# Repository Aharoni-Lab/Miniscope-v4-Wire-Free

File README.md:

# Miniscope-v4-Wire-Free

The Miniscope v4 Wire-Free is an open-source one photon miniatirized microscope for neural recordings in freely behaving animals.  

This microscope is based on the Miniscope v4, sharing the same optical properties with redesigned electronics. For more information check our wiki page: https://wiki.aharoni-lab.com/Wire-free_Miniscope_v4

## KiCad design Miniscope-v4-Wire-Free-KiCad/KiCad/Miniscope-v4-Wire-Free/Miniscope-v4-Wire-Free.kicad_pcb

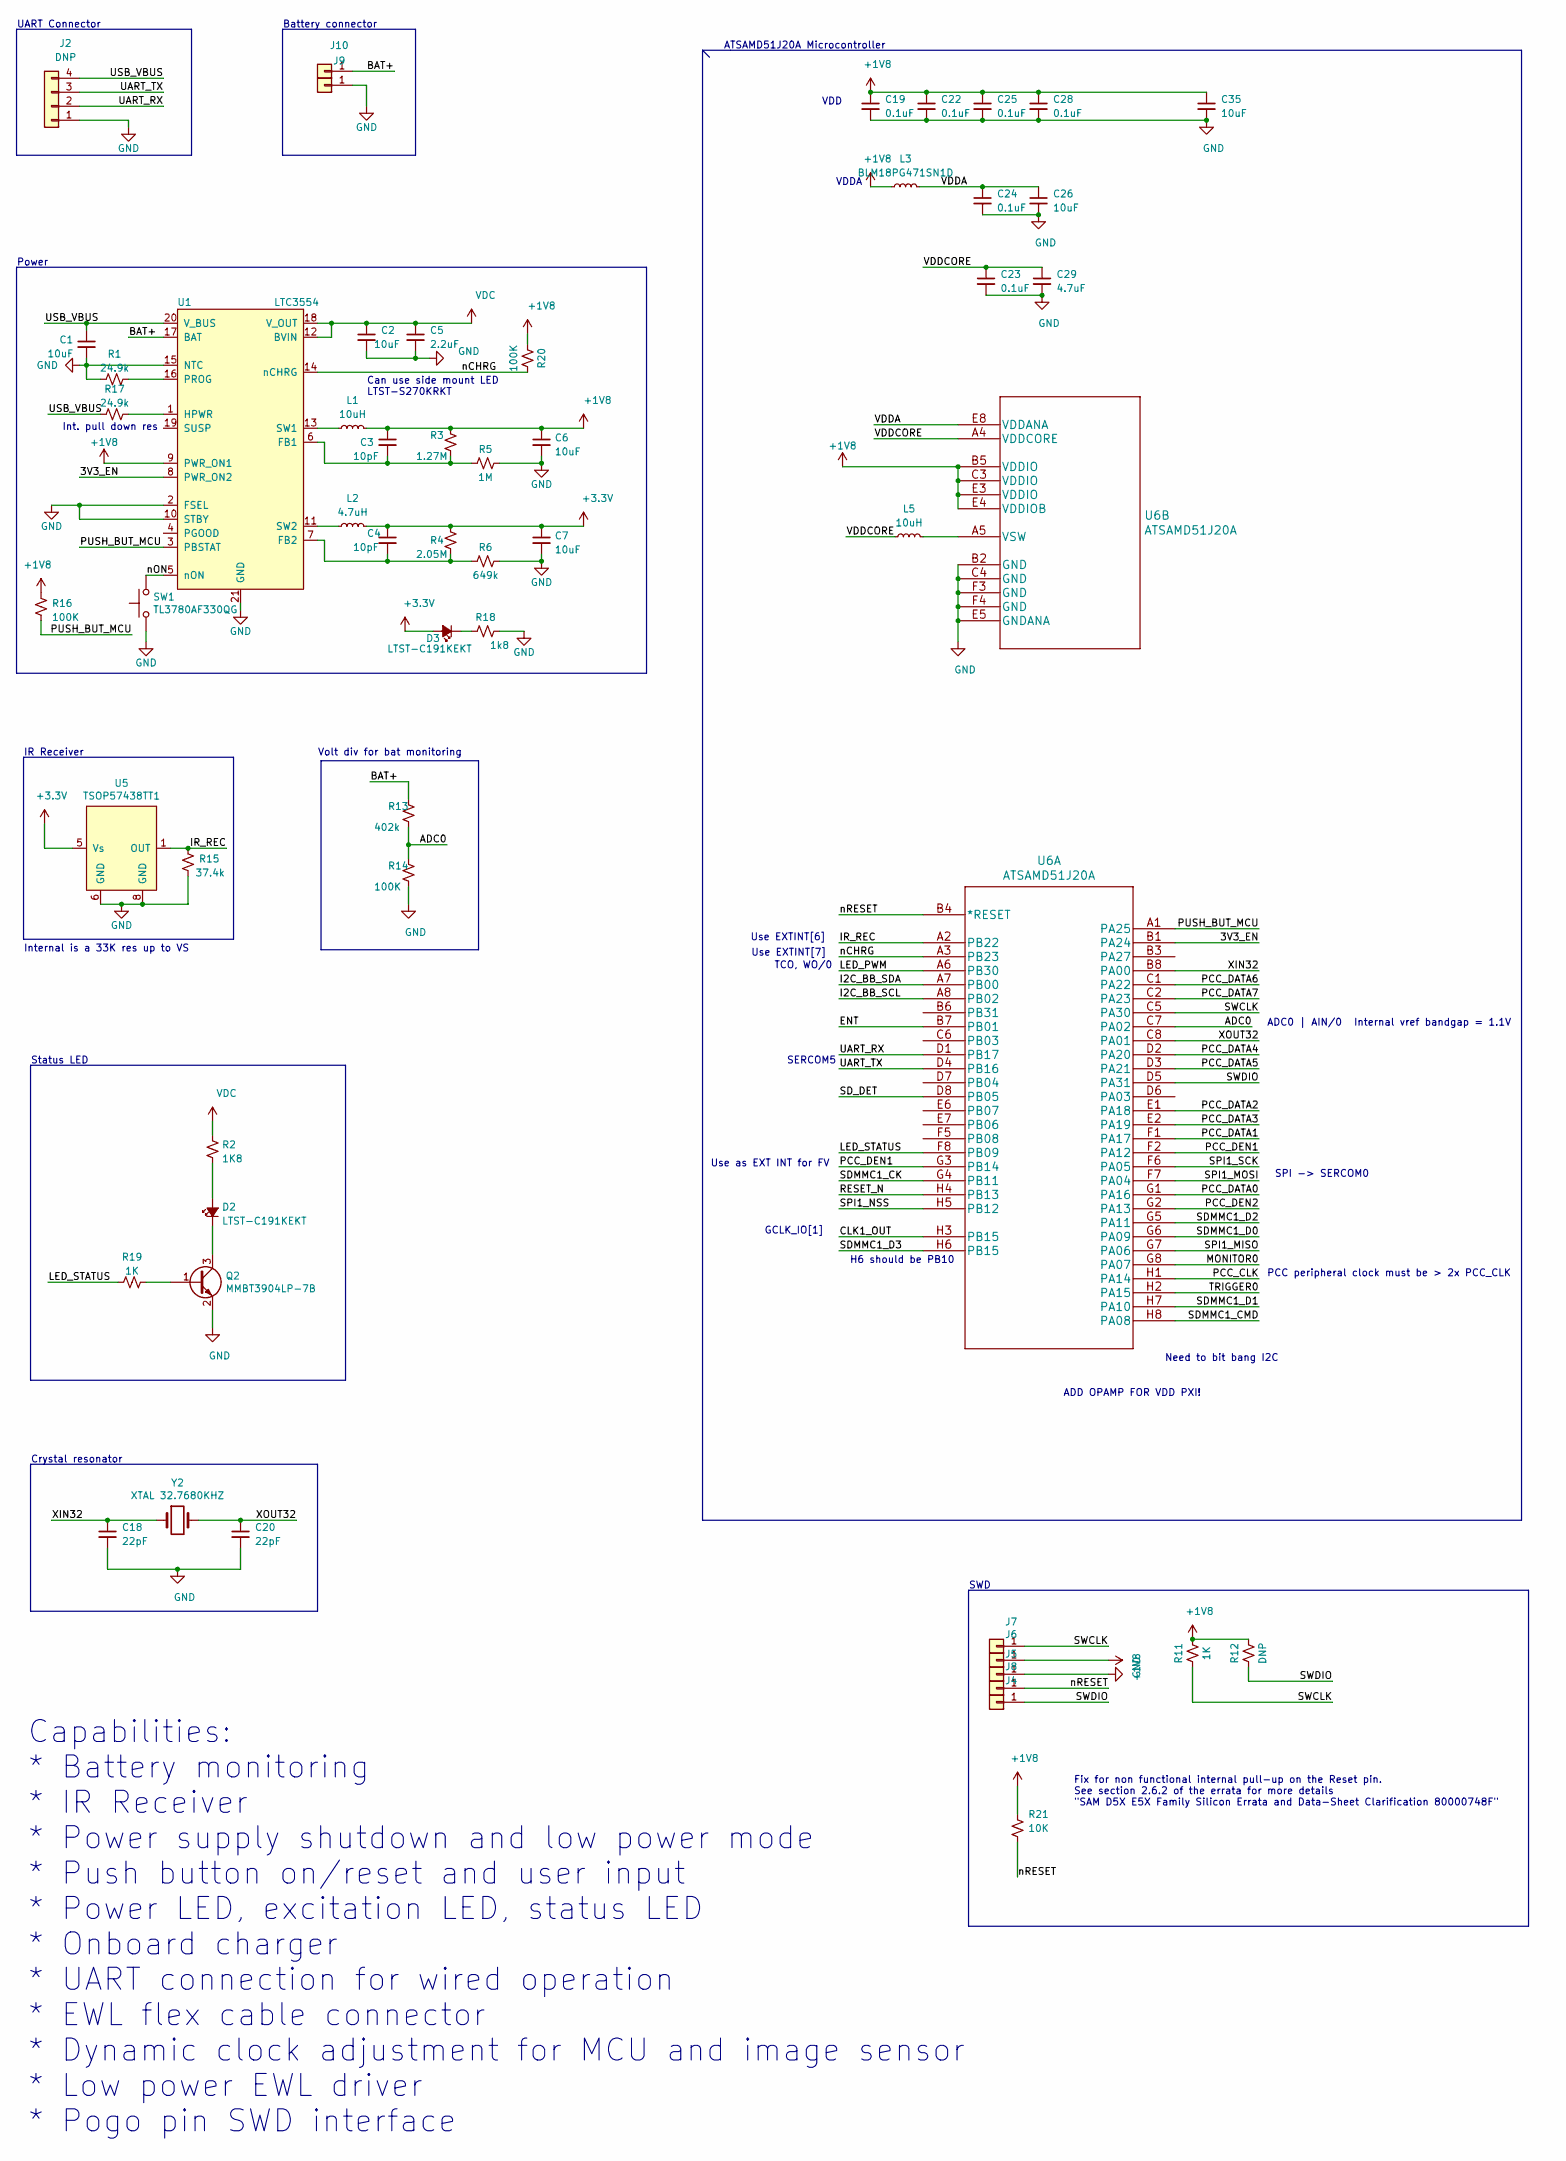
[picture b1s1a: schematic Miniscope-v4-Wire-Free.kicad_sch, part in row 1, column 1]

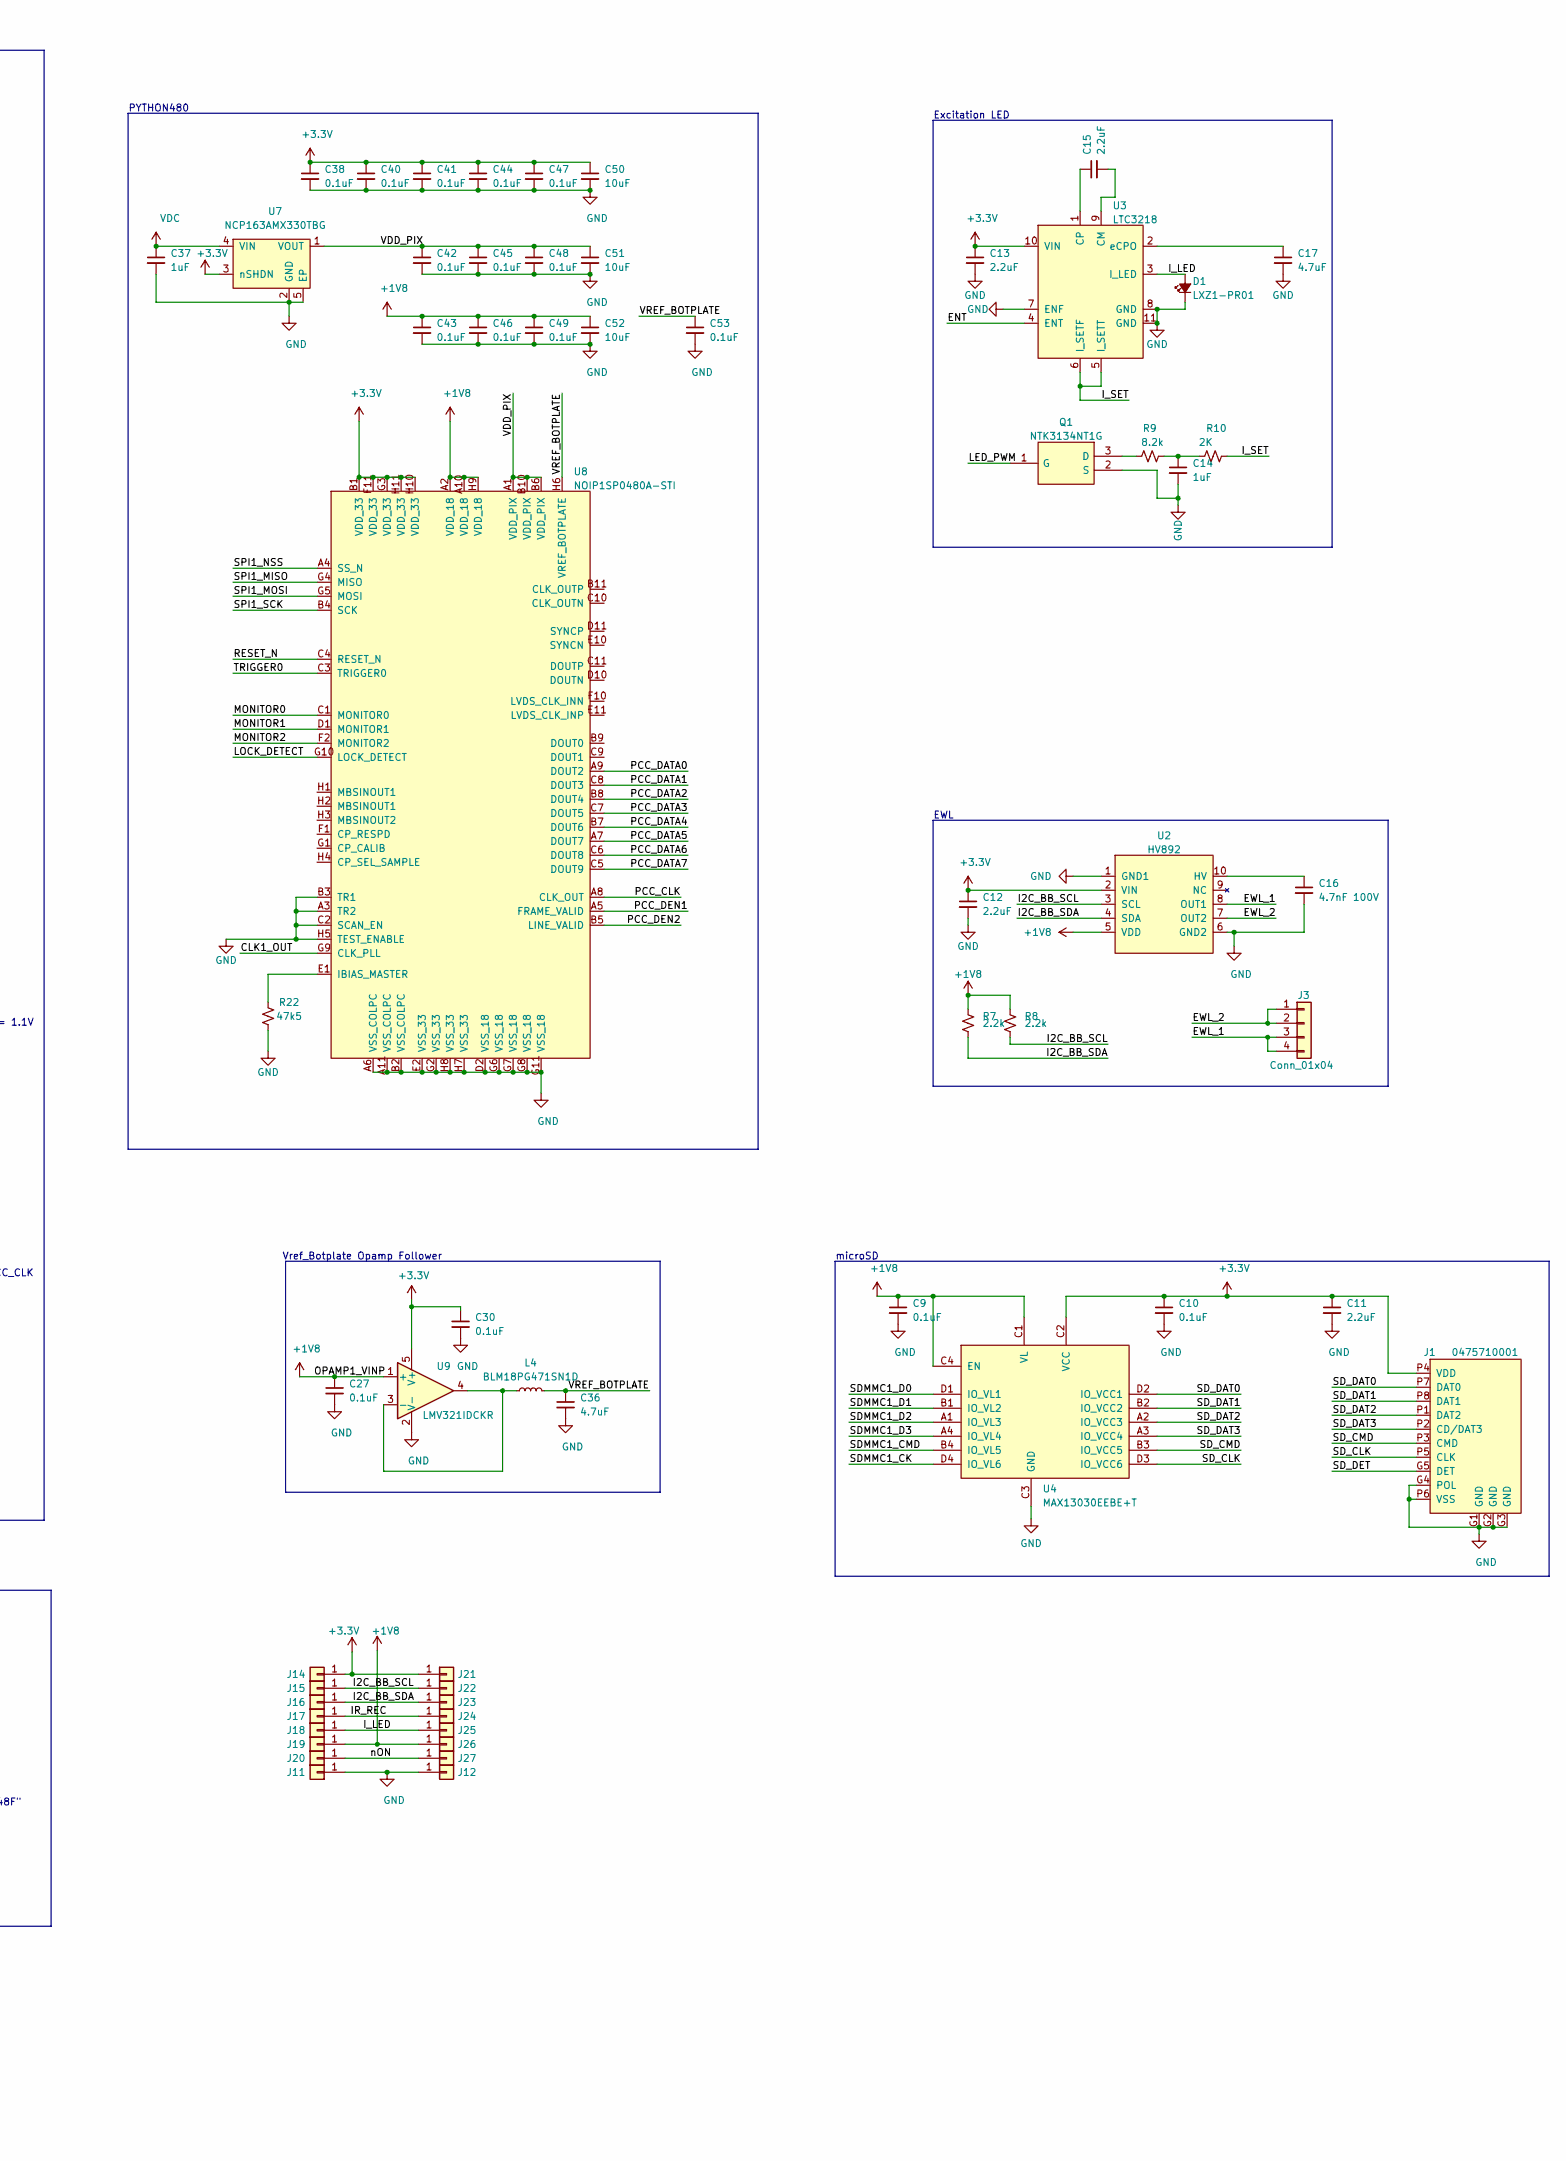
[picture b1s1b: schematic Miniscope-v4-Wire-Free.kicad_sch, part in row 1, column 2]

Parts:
C1, C2, C6, C7, C26, C35, C50, C51, C52: 10uF; C_0402_1005Metric_L; MPN CL05A106MP5NUNC
C3, C4: 10pF; C_0201_0603Metric_L; MPN GRM0335C1H100JA01J
C5, C11, C12, C13, C15: 2.2uF; C_0201_0603Metric_L; MPN CM03X5R225M10AH
C9, C10, C19, C22, C23, C24, C25, C27, C28, C30, C38, C40, C41, C42, C43, C44, C45, C46, C47, C48, C49, C53: 0.1uF; C_0201_0603Metric_L; MPN GRM033R61E104KE14J
C14, C37: 1uF; C_0201_0603Metric_L; MPN CL03A105MO3NRNH
C16: 4.7nF 100V; C_0603_1608Metric_L; MPN 885012206112
C17, C29, C36: 4.7uF; C_0201_0603Metric_L; MPN GRM035R60J475ME15D
C18, C20: 22pF; C_0201_0603Metric_L; MPN GRM0335C1H270GA01D
D1: LXZ1-PR01; LED_LXZ1_PR01_L; MPN LXZ1-PR01
D2, D3: LTST-C191KEKT; LED_SC80X160X65L40L; MPN LTST-C191KEKT
J1: 0475710001; MPN 0475710001
J2: DNP; 1x4_USB; MPN n.a.
J3: Conn_01x04; FH19C-4S-0.5SH(10); MPN FH19C-4S-0.5SH(10)
J4, J5, J6, J7, J8, J9, J10, J11, J12, J14, J15, J16, J17, J18, J19, J20, J21, J22, J23, J24, J25, J26, J27: DNP; Conn_1x1_700_Circular_Pad; MPN n.a.
L1, L5: 10uH; C_0805_2012Metric_L; MPN MLZ1608N100LT000
L2: 4.7uH; C_0805_2012Metric_L; MPN MLP2012S4R7MT0S1
L3, L4: BLM18PG471SN1D; L_0603_1608Metric_L; MPN BLM18PG471SN1D
Q1: NTK3134NT1G; TRXSOFL3P40_120X120X55L29X21L; Manufacturer_Part_Number NTK3134NT1G; Mouser Part Number 863-NTK3134NT1G
Q2: MMBT3904LP-7B; TRXDFN3_101X61X53L25X15N; MPN MMBT3904LP-7B
R1, R17: 24.9k; R_0201_0603Metric_ERJ_L; MPN CRCW020124K9FNED
R2: 1K8; R_0201_0603Metric_ERJ_L; MPN ERJ-1GNF1801C
R3: 1.27M; R_0201_0603Metric_ERJ_L; MPN CRCW02011M27FNED
R4: 2.05M; R_0201_0603Metric_ERJ_L; MPN CRCW02012M05FNED
R5: 1M; R_0201_0603Metric_ERJ_L; MPN CRCW02011M00FNED
R6: 649k; R_0201_0603Metric_ERJ_L; MPN RC0201FR-07649KL
R7, R8: 2.2k; R_0201_0603Metric_ERJ_L; MPN RC0201FR-072K2L
R9: 8.2k; R_0201_0603Metric_ERJ_L; MPN ERJ-1GNF8201C
R10: 2K; R_0201_0603Metric_ERJ_L; MPN RC0201FR-072KL
R11, R19: 1K; R_0201_0603Metric_ERJ_L; MPN RC0201FR-071KL
R12: DNP; R_0201_0603Metric_ERJ_L; MPN n.a.
R13: 402k; R_0201_0603Metric_ERJ_L; MPN ERJ-1GNF4023C
R14, R16, R20: 100K; R_0201_0603Metric_ERJ_L; MPN ERJ-1GNF1003C
R15: 37.4k; R_0201_0603Metric_ERJ_L; MPN ERJ-1GNF3742C
R18: 1k8; R_0201_0603Metric_ERJ_L; MPN ERJ-1GNF1801C
R21: 10K; R_0201_0603Metric_ERJ_L; MPN ERJ-1GNF1002C
R22: 47k5; R_0201_0603Metric_ERJ_L; MPN ERJ-1GNF4752C
SW1: TL3780AF330QG; SMD-Switch-3mmx2mm; MPN TL3780AF330QG
U1: LTC3554; QFN-20-1EP_3x3mm_P0.4mm_EP1.65x1.65mm; MPN LTC3554EUD#PBF
U2: HV892; SON11P65_400X400X80L40X30T315X255L; MPN HV892K7-G
U3: LTC3218; SON_11_P50_300X200X80L40X25T239X64L; MPN LTC3218EDDB#TRMPBF
U4: MAX13030EEBE+T; BGA-16_1.92x1.92mm_Layout4x4_P0.5mm; MPN MAX13030EEBE+T
U5: TSOP57438TT1; SON_4_P300_395X395X90L55X35L; MPN TSOP57438TT1
U6: ATSAMD51J20A; ATSAMD51J20A-UUT-EFP; MPN ATSAMD51J20A-UUT-EFP
U7: NCP163AMX330TBG; UQFN_MCP1711; MPN NCP163AMX330TBG
U8: NOIP1SP0480A-STI; BGA88CP50_8X11_493X613X75B25; MPN NOIP1SP0480A-STI
U9: LMV321IDCKR; SOT_23-5P65_210X110L36X22L; MPN LMV321IDCKR
Y2: XTAL 32.7680KHZ; Crystal_SMD_MicroCrystal_CC8V-T1A-2Pin_2.0x1.2mm; MPN 9HT11-32.768KBZF-T

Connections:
+1V8: C3.1, C6.1, C9.1, C19.1, C22.1, C25.1, C27.1, C28.1, C35.1, C43.1, C46.1, C49.1, C52.1, J6.1, J19.1, J26.1, L1.2, L3.1, R3.1, R7.1, R8.1, R11.1, R12.1, R16.1, R20.2, R21.1, U1.9 (PWR_ON1), U2.5 (VDD), U4.C1 (VL), U4.C4 (EN), U6.B5 (VDDIO), U6.C3 (VDDIO), U6.E3 (VDDIO), U6.E4 (VDDIOB), U8.A2 (VDD_18), U8.A10 (VDD_18), U8.H9 (VDD_18), U9.1 (+)
+3V3: C4.1, C7.1, C10.1, C11.1, C12.1, C13.1, C30.1, C38.1, C40.1, C41.1, C44.1, C47.1, C50.1, D3.2 (A), J1.P4 (VDD), J14.1, J21.1, L2.2, R4.1, U2.2 (VIN), U3.10 (VIN), U4.C2 (VCC), U5.5 (Vs), U7.3 (nSHDN), U8.B1 (VDD_33), U8.F11 (VDD_33), U8.G3 (VDD_33), U8.H10 (VDD_33), U8.H11 (VDD_33), U9.5 (V+)
/3V3_EN: U1.8 (PWR_ON2), U6.B1 (PA24)
/ADC0: R13.2, R14.1, U6.C7 (PA02)
/BAT+: J10.1, R13.1, U1.17 (BAT)
/CLK1_OUT: U6.H3 (PB15), U8.G9 (CLK_PLL)
/ENT: U3.4 (ENT), U6.B7 (PB01)
/EWL_1: J3.3, J3.4, U2.8 (OUT1)
/EWL_2: J3.1, J3.2, U2.7 (OUT2)
/I2C_BB_SCL: J15.1, J22.1, R8.2, U2.3 (SCL), U6.A8 (PB02)
/I2C_BB_SDA: J16.1, J23.1, R7.2, U2.4 (SDA), U6.A7 (PB00)
/IR_REC: J17.1, J24.1, R15.1, U5.1 (OUT), U6.A2 (PB22)
/I_LED: D1.A, J18.1, J25.1, U3.3 (I_LED)
/I_SET: R10.1, U3.5 (I_SETT), U3.6 (I_SETF)
/LED_PWM: Q1.1 (G), U6.A6 (PB30)
/LED_STATUS: R19.2, U6.F8 (PB09)
/LOCK_DETECT: U8.G10 (LOCK_DETECT)
/MONITOR0: U6.G8 (PA07), U8.C1 (MONITOR0)
/MONITOR1: U8.D1 (MONITOR1)
/MONITOR2: U8.F2 (MONITOR2)
/PCC_CLK: U6.H1 (PA14), U8.A8 (CLK_OUT)
/PCC_DATA0: U6.G1 (PA16), U8.A9 (DOUT2)
/PCC_DATA1: U6.F1 (PA17), U8.C8 (DOUT3)
/PCC_DATA2: U6.E1 (PA18), U8.B8 (DOUT4)
/PCC_DATA3: U6.E2 (PA19), U8.C7 (DOUT5)
/PCC_DATA4: U6.D2 (PA20), U8.B7 (DOUT6)
/PCC_DATA5: U6.D3 (PA21), U8.A7 (DOUT7)
/PCC_DATA6: U6.C1 (PA22), U8.C6 (DOUT8)
/PCC_DATA7: U6.C2 (PA23), U8.C5 (DOUT9)
/PCC_DEN1: U6.F2 (PA12), U6.G3 (PB14), U8.A5 (FRAME_VALID)
/PCC_DEN2: U6.G2 (PA13), U8.B5 (LINE_VALID)
/PUSH_BUT_MCU: R16.2, U1.3 (PBSTAT), U6.A1 (PA25)
/RESET_N: U6.H4 (PB13), U8.C4 (RESET_N)
/SDMMC1_CK: U4.D4 (IO_VL6), U6.G4 (PB11)
/SDMMC1_CMD: U4.B4 (IO_VL5), U6.H8 (PA08)
/SDMMC1_D0: U4.D1 (IO_VL1), U6.G6 (PA09)
/SDMMC1_D1: U4.B1 (IO_VL2), U6.H7 (PA10)
/SDMMC1_D2: U4.A1 (IO_VL3), U6.G5 (PA11)
/SDMMC1_D3: U4.A4 (IO_VL4), U6.H6 (PB15)
/SD_CLK: J1.P5 (CLK), U4.D3 (IO_VCC6)
/SD_CMD: J1.P3 (CMD), U4.B3 (IO_VCC5)
/SD_DAT0: J1.P7 (DAT0), U4.D2 (IO_VCC1)
/SD_DAT1: J1.P8 (DAT1), U4.B2 (IO_VCC2)
/SD_DAT2: J1.P1 (DAT2), U4.A2 (IO_VCC3)
/SD_DAT3: J1.P2 (CD/DAT3), U4.A3 (IO_VCC4)
/SD_DET: J1.G5 (DET), U6.D8 (PB05)
/SPI1_MISO: U6.G7 (PA06), U8.G4 (MISO)
/SPI1_MOSI: U6.F7 (PA04), U8.G5 (MOSI)
/SPI1_NSS: U6.H5 (PB12), U8.A4 (SS_N)
/SPI1_SCK: U6.F6 (PA05), U8.B4 (SCK)
/SWCLK: J7.1, R11.2, U6.C5 (PA30)
/SWDIO: J4.1, R12.2, U6.D5 (PA31)
/TRIGGER0: U6.H2 (PA15), U8.C3 (TRIGGER0)
/UART_RX: J2.2, U6.D1 (PB17)
/UART_TX: J2.3, U6.D4 (PB16)
/USB_VBUS: C1.1, J2.4, R17.2, U1.20 (V_BUS)
/VDDA: C24.1, C26.1, L3.2, U6.E8 (VDDANA)
/VDDCORE: C23.1, C29.1, L5.1, U6.A4 (VDDCORE)
/VDD_PIX: C42.1, C45.1, C48.1, C51.1, U7.1 (VOUT), U8.A1 (VDD_PIX), U8.B6 (VDD_PIX), U8.B10 (VDD_PIX)
/VREF_BOTPLATE: C36.1, C53.1, L4.2, U8.H6 (VREF_BOTPLATE)
/XIN32: C18.1, U6.B8 (PA00), Y2.1
/XOUT32: C20.1, U6.C8 (PA01), Y2.2
/nCHRG: R20.1, U1.14 (nCHRG), U6.A3 (PB23)
/nON: J20.1, J27.1, SW1.2, U1.5 (nON)
/nRESET: J8.1, R21.2, U6.B4 (*RESET)
GND: C1.2, C2.2, C5.2, C6.2, C7.2, C9.2, C10.2, C11.2, C12.2, C13.2, C14.2, C16.2, C17.2, C18.2, C19.2, C20.2, C22.2, C23.2, C24.2, C25.2, C26.2, C27.2, C28.2, C29.2, C30.2, C35.2, C36.2, C37.2, C38.2, C40.2, C41.2, C42.2, C43.2, C44.2, C45.2, C46.2, C47.2, C48.2, C49.2, C50.2, C51.2, C52.2, C53.2, D1.C, J1.G1 (GND), J1.G2 (GND), J1.G3 (GND), J1.G4 (POL), J1.P6 (VSS), J2.1, J5.1, J9.1, J11.1, J12.1, Q1.2 (S), Q2.2 (E), R1.2, R5.1, R6.1, R14.2, R15.2, R18.1, R22.2, SW1.1, U1.2 (FSEL), U1.10 (STBY), U1.15 (NTC), U1.21 (GND), U2.1 (GND1), U2.6 (GND2), U3.7 (ENF), U3.8 (GND), U3.11 (GND), U4.C3 (GND), U5.6 (GND), U5.8 (GND), U6.B2 (GND), U6.C4 (GND), U6.E5 (GNDANA), U6.F3 (GND), U6.F4 (GND), U7.2 (GND), U7.5 (EP), U8.A3 (TR2), U8.A6 (VSS_COLPC), U8.A11 (VSS_COLPC), U8.B2 (VSS_COLPC), U8.B3 (TR1), U8.C2 (SCAN_EN), U8.D2 (VSS_18), U8.E2 (VSS_33), U8.G2 (VSS_33), U8.G6 (VSS_18), U8.G7 (VSS_18), U8.G8 (VSS_18), U8.G11 (VSS_18), U8.H5 (TEST_ENABLE), U8.H7 (VSS_33), U8.H8 (VSS_33), U9.2 (V-)
unnamed: C3.2, R3.2, R5.2, U1.6 (FB1)
unnamed: C4.2, R4.2, R6.2, U1.7 (FB2)
unnamed: C14.1, R9.1, R10.2
unnamed: C15.1, U3.1 (CP)
unnamed: C15.2, U3.9 (CM)
unnamed: C16.1, U2.10 (HV)
unnamed: C17.1, U3.2 (eCPO)
unnamed: D2.1 (K), Q2.3 (C)
unnamed: D2.2 (A), R2.1
unnamed: D3.1 (K), R18.2
unnamed: L1.1, U1.13 (SW1)
unnamed: L2.1, U1.11 (SW2)
unnamed: L4.1, U9.3 (-), U9.4
unnamed: L5.2, U6.A5 (VSW)
unnamed: Q1.3 (D), R9.2
unnamed: Q2.1 (B), R19.1
unnamed: R1.1, U1.16 (PROG)
unnamed: R17.1, U1.1 (HPWR)
unnamed: R22.1, U8.E1 (IBIAS_MASTER)
VDC: C2.1, C5.1, C37.1, R2.2, U1.12 (BVIN), U1.18 (V_OUT), U7.4 (VIN)

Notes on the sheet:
Internal is a 33K res up to VS
Need to bit bang I2C
Fix for non functional internal pull-up on the Reset pin. See section 2.6.2 of the errata for more details "SAM D5X E5X Family Silicon Errata and Data-Sheet Clarification 80000748F"
Crystal resonator
Use as EXT INT for FV
SERCOM5
Excitation LED
Vref_Botplate Opamp Follower
H6 should be PB10
PCC peripheral clock must be > 2x PCC_CLK
Power
Internal vref bandgap = 1.1V
IR Receiver
UART Connector
Use EXTINT[7]
SPI -> SERCOM0
Can use side mount LED LTST-S270KRKT
Int. pull down res
EWL
ADC0 | AIN/0
VDD
Capabilities: * Battery monitoring * IR Receiver * Power supply shutdown and low power mode * Push button on/reset and user input * Power LED, excitation LED, status LED * Onboard charger * UART connection for wired operation * EWL flex cable connector * Dynamic clock adjustment for MCU and image s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
SWD
TCO, WO/0
Status LED
Volt div for bat monitoring
Battery connector
VDDA
ADD OPAMP FOR VDD PXI!
PYTHON480
Use EXTINT[6]
GCLK_IO[1]
ATSAMD51J20A Microcontroller
microSD

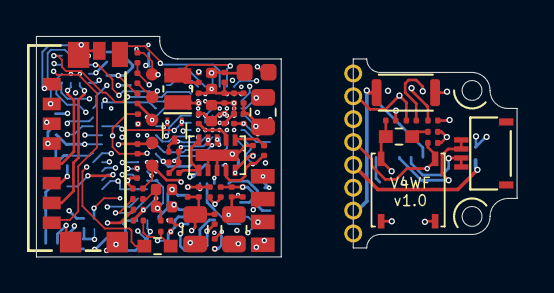
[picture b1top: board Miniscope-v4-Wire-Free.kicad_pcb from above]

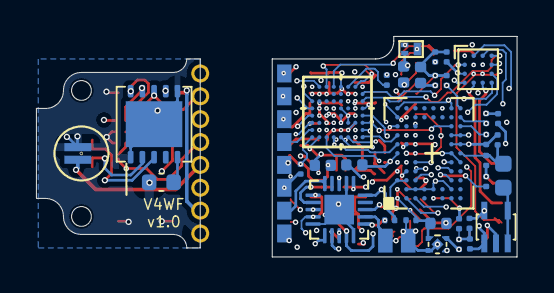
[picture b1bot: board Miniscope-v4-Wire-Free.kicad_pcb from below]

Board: 6 copper layers, 13.6 x 12.2 mm, 117 parts (44 on the bottom side), 83 nets.

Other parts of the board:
Mount: Conn_1x1_700_Circular_Pad
Mount#2: Conn_1x1_700_Circular_Pad

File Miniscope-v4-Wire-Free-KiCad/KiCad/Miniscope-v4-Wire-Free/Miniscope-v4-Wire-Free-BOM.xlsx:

Item | Quantity | Reference(s) | Value | Description | Manufacturer Name | Manufacturer Part Number
1 | 9 | C1, C2, C6, C7, C26, C35, C50, C51, C52 | 10uF | CAP CER 10UF 6.3V X5R 0402 | Murata | GRM155R60J106ME15D
2 | 2 | C3, C4 | 10pF | CAP CER 10PF 50V C0G/NP0 0201 | Murata | GRM0335C1H100FA01J
3 | 5 | C5, C11, C12, C13, C15 | 2.2uF | CAP CER 2.2UF 10V X5R 0201 | Murata | GRM033R61A225KE47D
4 | 22 | C9, C10, C19, C22, C23, C24, C25, C27, C28, C30, C38, C40, C41, C42, C43, C44, 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 | 0.1uF | CAP CER 0.1UF 25V X5R 0201 | Murata | GRM033R61E104KE14J
5 | 2 | C14, C37 | 1uF | CAP CER 1UF 10V X5R 0201 | Murata | GRM033R61A105ME15D
6 | 1 | C16 | 4.7nF 100V | CAP CER 4700PF 100V X7R 0603 | Murata | GCM188R72A472KA37D
7 | 3 | C17, C29, C36 | 4.7uF | CAP CER 4.7UF 6.3V X5R 0201 | Murata | GRM035R60J475ME15D
8 | 2 | C18, C20 | 22pF | CAP CER 22PF 50V C0G/NP0 0201 | Murata | GRM0335C1H220GA01D
9 | 1 | D1 | LXZ1-PB01 | LED LUXEON Z BLUE 470NM SMD | Lumileds | LXZ1-PB01
10 | 2 | D2,D3 | RED LED | LED RED CLEAR THIN 0603 SMD | Lite-On Inc. | LTST-C191KEKT
11 | 1 | J1 | 475710001 | CONN MICRO SD CARD PUSH-PULL R/A | Molex | 475710001
12 | 2 | L1, L5 | 10uH | FIXED IND 10UH 300MA 600MOHM SMD | TDK | MLZ1608N100LT000
13 | 1 | L2 | 4.7uH | FIXED IND 4.7UH 180MA 300MOHM SM | Abracon | ASMCI-0805-4R7M-T
14 | 2 | L3, L4 | BLM18PG471SN1D | FERRITE BEAD 470 OHM 0603 1LN | Murata | BLM18PG471SN1D
15 | 1 | Q1 | NTK3134NT1G | Power MOSFET | ON Semiconductor | NTK3134NT1G
16 | 1 | Q2 | MMBT3904LP-7B | TRANS NPN 40V 0.2A DFN1006-3 | Diodes Incorporated | MMBT3904LP-7B
17 | 2 | R1, R17 | 25K | RES SMD 24.9K OHM 1% 1/20W 0201 | Vishay Dale | CRCW020124K9FNED
18 | 2 | R2, R18 | 1.8K | RES SMD 1.8K OHM 1% 1/20W 0201 | Panasonic | ERJ-1GNF1801C
19 | 1 | R3 | 1.25M | RES 1.27M OHM 1% 1/20W 0201 | Vishay Dale | CRCW02011M27FNED
20 | 1 | R4 | 2.05M | RES 2.05M OHM 1% 1/20W 0201 | Vishay Dale | CRCW02012M05FNED
21 | 1 | R5 | 1M | RES SMD 1M OHM 1% 1/20W 0201 | Vishay Dale | CRCW02011M00FNED
22 | 1 | R6 | 649K | RES SMD 649K OHM 1% 1/20W 0201 | Vishay Dale | CRCW0201649KFNED
23 | 2 | R7, R8 | 2.2K | RES SMD 2.2K OHM 1% 1/20W 0201 | Panasonic | ERJ-1GNF2201C
24 | 1 | R9 | 8.2K | RES SMD 8.2K OHM 1% 1/20W 0201 | Vishay Dale | CRCW02018K20FKED
25 | 1 | R10 | 2K | RES SMD 2K OHM 1% 1/20W 0201 | Vishay Dale | CRCW02012K00FNED
26 | 2 | R11, R19 | 1K | RES SMD 1K OHM 1% 1/20W 0201 | Vishay Dale | CRCW02011K00FKED
27 | 1 | R12 | DNL | DNL | DNL | DNL
28 | 1 | R13 | 400K | RES SMD 402K OHM 1% 1/20W 0201 | Panasonic | ERJ-1GNF4023C
29 | 3 | R14, R16, R20 | 100K | RES SMD 100K OHM 1% 1/20W 0201 | Panasonic | ERJ-1GNF1003C
30 | 1 | R15 | 37K | RES SMD 37.4K OHM 1% 1/20W 0201 | Panasonic | ERJ-1GNF3742C
31 | 1 | R21 | 47k5 | RES SMD 47.5K OHM 1% 1/20W 0201 | Vishay Dale | CRCW020147K5FNED
32 | 1 | R22 | 10K | RES SMD 1K OHM 1% 1/20W 0201 | Vishay Dale | CRCW02011K00FKED
33 | 1 | SW1 | TL3780AF330QG | SWITCH TACTILE SPST-NO 0.02A 15V | E-Switch | TL3780AF330QG
34 | 1 | U1 | LTC3554 | IC USB POWER MANAGER 20UTQFN | Analog Devices Inc. | LTC3554EUD#PBF
35 | 1 | U2 | HV892 | IC LED DRIVER LENS 10WDFN | Microchip | HV892K7-G
36 | 1 | U3 | LTC3218 | IC LED DRIVER RGLTR 150MA 10DFN | Analog Devices Inc. | LTC3218
37 | 1 | U4 | MAX13030EETE+BGA | IC TRNSLTR BIDIRECTIONAL 16TQFN | Maxim Integrated | MAX13030EETE+
38 | 1 | U5 | TSOP57438TT1 | SENSOR REMOTE REC 38.0KHZ 40M | Vishay Semiconductor Opto Division | TSOP57438TT1
39 | 1 | U6 | ATSAMD51J20A-UUT-EFP | MCU 120MHZ 1024KB FLASH 64 | Microchip | ATSAMD51J20A-UUT-EFP
40 | 1 | U7 | NCP163AMX330TBG | IC REG LINEAR 3.3V 250MA 4XDFN | onsemi | NCP163AMX330TBG
41 | 1 | U8 | NOIP1SN0480A | IC CMOS IMAGE SENSOR 1/3.6" | onsemi | NOIP1SN0480A-STI1
42 | 1 | U9 | LMV321IDCKR | IC OPAMP GP 1 CIRCUIT SC70-5 | Texas Instruments | LMV321IDCKR
43 | 1 | J3 | FH19C-4S-0.5SH | CONN FFC BOTTOM 4POS 0.5MM R/A | Hirose | FH19C-4S-0.5SH(10)
44 | 1 | Y2 | Crystal | CRYSTAL 32.7680KHZ 12.5PF SMD | TXC CORPORATION | 9HT11-32.768KBZF-T
Total | 91

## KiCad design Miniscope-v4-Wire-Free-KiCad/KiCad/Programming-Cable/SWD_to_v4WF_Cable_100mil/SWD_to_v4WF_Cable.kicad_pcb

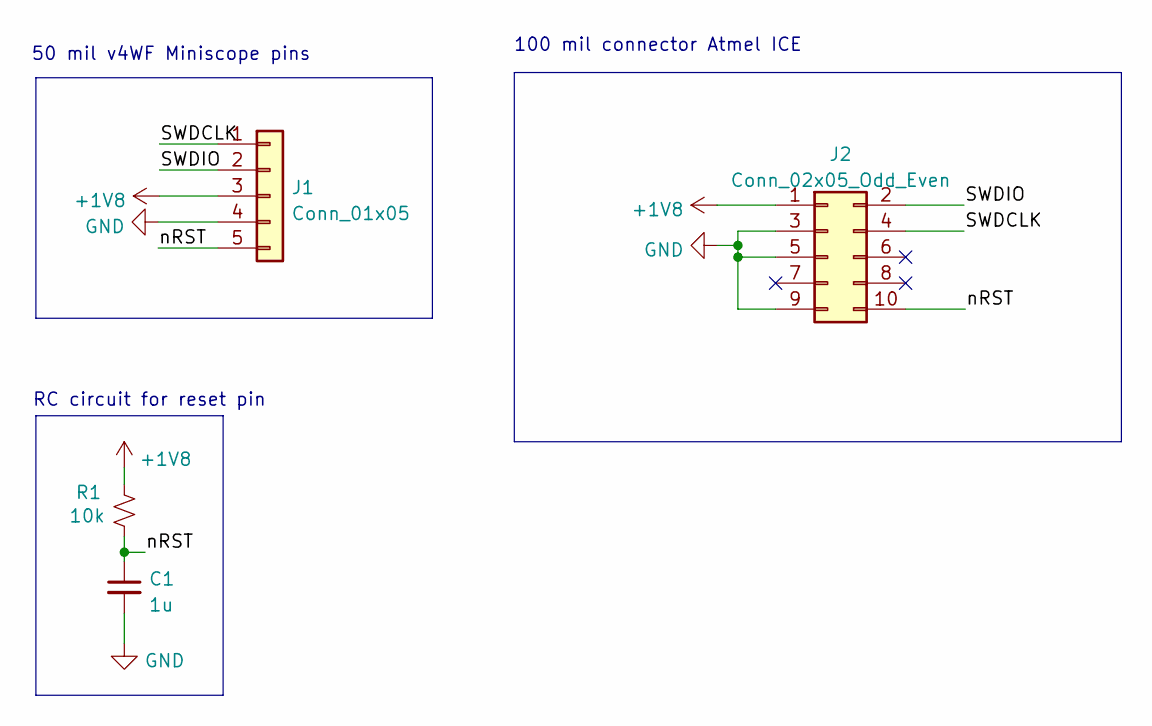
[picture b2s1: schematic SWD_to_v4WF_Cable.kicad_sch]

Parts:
C1: 1u; C_0805_2012Metric_Pad1.18x1.45mm_HandSolder
J1: Conn_01x05; PinHeader_1x05_P2.54mm_Vertical
J2: Conn_02x05_Odd_Even; PinHeader_2x05_P2.54mm_Horizontal
R1: 10k; R_0805_2012Metric_Pad1.20x1.40mm_HandSolder

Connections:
+1V8: J1.3, J2.1, R1.1
/SWDCLK: J1.1, J2.4
/SWDIO: J1.2, J2.2
/nRST: C1.1, J1.5, J2.10, R1.2
GND: C1.2, J1.4, J2.3, J2.5, J2.9

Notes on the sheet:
RC circuit for reset pin
50 mil v4WF Miniscope pins
100 mil connector Atmel ICE

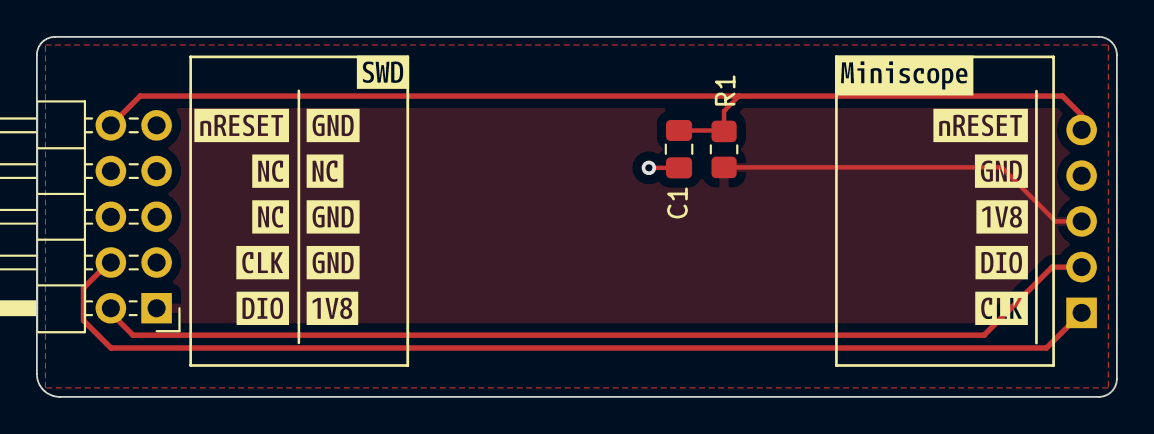
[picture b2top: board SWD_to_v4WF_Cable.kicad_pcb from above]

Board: 2 copper layers, 60.0 x 20.0 mm, 21 parts (1 on the bottom side), 5 nets.

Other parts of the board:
kibuzzard-630EA2F1: G***; kibuzzard-630EA2F1
kibuzzard-630EA6B9: G***; kibuzzard-630EA6B9
kibuzzard-630EA6CF: G***; kibuzzard-630EA6CF
kibuzzard-630EA6DD: G***; kibuzzard-630EA6DD
kibuzzard-630EA6F1: G***; kibuzzard-630EA6F1
kibuzzard-630EA36E: G***; kibuzzard-630EA36E
kibuzzard-630EA39E: G***; kibuzzard-630EA39E
kibuzzard-630EA059: G***; kibuzzard-630EA059
kibuzzard-630EA251, kibuzzard-630EA251#2, kibuzzard-630EA251#3: G***; kibuzzard-630EA251
kibuzzard-630EA342, kibuzzard-630EA342#2, kibuzzard-630EA342#3: G***; kibuzzard-630EA342
kibuzzard-630EA384: G***; kibuzzard-630EA384
kibuzzard-630EA721: G***; kibuzzard-630EA721
kibuzzard-630EA733: G***; kibuzzard-630EA733

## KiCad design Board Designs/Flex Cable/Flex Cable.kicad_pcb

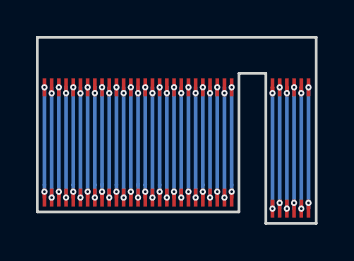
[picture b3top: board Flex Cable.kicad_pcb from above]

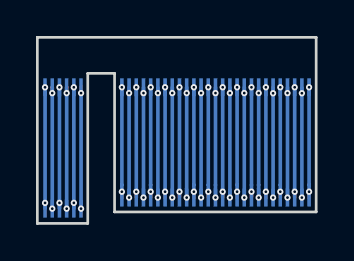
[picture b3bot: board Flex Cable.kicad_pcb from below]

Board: 2 copper layers, 15.5 x 10.3 mm, 8 parts (4 on the bottom side), 33 nets.

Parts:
J1, J2, J5, J6: Conn_01x27; B2B_Flex_27_Single_Row_200x1000_Pad_400P
J3, J4, J7, J8: Conn_01x06; B2B_Flex_6_Single_Row_200x1000_Pad_400P

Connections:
unnamed: J1.1, J2.1, J5.1, J6.1
unnamed: J1.2, J2.2, J5.2, J6.2
unnamed: J1.3, J2.3, J5.3, J6.3
unnamed: J1.4, J2.4, J5.4, J6.4
unnamed: J1.5, J2.5, J5.5, J6.5
unnamed: J1.6, J2.6, J5.6, J6.6
unnamed: J1.7, J2.7, J5.7, J6.7
unnamed: J1.8, J2.8, J5.8, J6.8
unnamed: J1.9, J2.9, J5.9, J6.9
unnamed: J1.10, J2.10, J5.10, J6.10
unnamed: J1.11, J2.11, J5.11, J6.11
unnamed: J1.12, J2.12, J5.12, J6.12
unnamed: J1.13, J2.13, J5.13, J6.13
unnamed: J1.14, J2.14, J5.14, J6.14
unnamed: J1.15, J2.15, J5.15, J6.15
unnamed: J1.16, J2.16, J5.16, J6.16
unnamed: J1.17, J2.17, J5.17, J6.17
unnamed: J1.18, J2.18, J5.18, J6.18
unnamed: J1.19, J2.19, J5.19, J6.19
unnamed: J1.20, J2.20, J5.20, J6.20
unnamed: J1.21, J2.21, J5.21, J6.21
unnamed: J1.22, J2.22, J5.22, J6.22
unnamed: J1.23, J2.23, J5.23, J6.23
unnamed: J1.24, J2.24, J5.24, J6.24
unnamed: J1.25, J2.25, J5.25, J6.25
unnamed: J1.26, J2.26, J5.26, J6.26
unnamed: J1.27, J2.27, J5.27, J6.27
unnamed: J3.1, J4.1, J7.1, J8.1
unnamed: J3.2, J4.2, J7.2, J8.2
unnamed: J3.3, J4.3, J7.3, J8.3
unnamed: J3.4, J4.4, J7.4, J8.4
unnamed: J3.5, J4.5, J7.5, J8.5
unnamed: J3.6, J4.6, J7.6, J8.6

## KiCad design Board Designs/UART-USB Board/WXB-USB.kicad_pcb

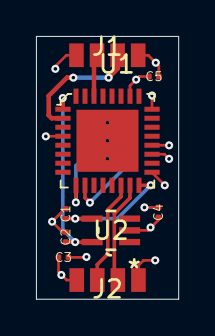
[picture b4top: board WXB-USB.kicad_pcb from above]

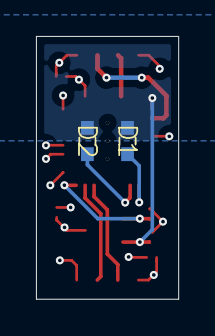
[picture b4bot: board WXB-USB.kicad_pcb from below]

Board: 4 copper layers, 7.9 x 14.6 mm, 11 parts (2 on the bottom side), 10 nets.

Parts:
C1, C4: GRM033R61A104ME15D; C_0201_0603Metric_L
C2: CC0201MRX5R4BB474; C_0201_0603Metric_L
C3, C5: GRM033R71A103KA01D; C_0201_0603Metric_L
D1: LTST-C190CKT; LED_SC80X160X65L40L
D2: TLMY1000-GS08; LED_SC80X160X65L40L
J1, J2: Conn_01x04; 1x4_USB
U1: FT232RQ-REEL; QFN-32-1EP_5x5mm
U2: TPS79718DCKR; DCK5

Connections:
+1V8: C2.1, D1.2, D2.2, U1.1, U2.5
+3V3: C1.1, U1.16, U2.4
/FT-WF-URX: J1.2, U1.2
/FT-WF-UTX: J1.3, U1.30
/USBD+: J2.2, U1.14
/USBD-: J2.3, U1.15
GND: C1.2, C2.2, C3.2, C4.2, C5.2, J1.4, J2.4, U1.4, U1.17, U1.20, U1.24, U1.26, U2.2
unnamed: D1.1, U1.9
unnamed: D2.1, U1.10
VBUS: C3.1, C4.1, C5.1, J1.1, J2.1, U1.19

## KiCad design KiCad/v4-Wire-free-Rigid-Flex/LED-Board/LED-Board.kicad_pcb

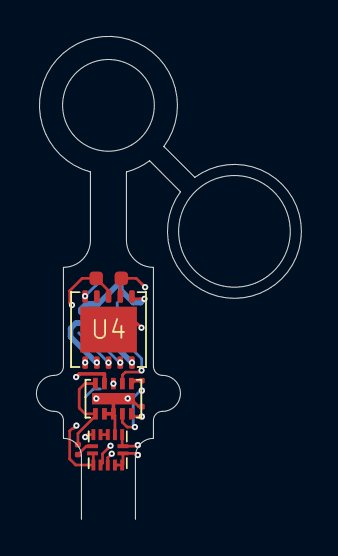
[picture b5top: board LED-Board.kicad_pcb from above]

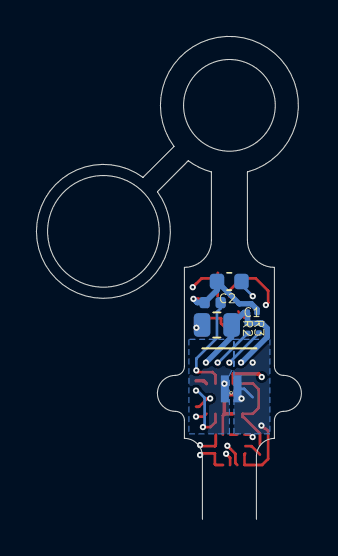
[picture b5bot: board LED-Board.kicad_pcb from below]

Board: 6 copper layers, 14.7 x 26.8 mm, 16 parts (7 on the bottom side), 14 nets.

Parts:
C1, C3, C4: GRM033R61A225ME47D; C_0201_0603Metric_L
C2: CL10B472KC8WPJC; C_0603_1608Metric_L
C5: GRM155R60J475ME47D; C_0402_1005Metric_L
C6: GRM033R61A104ME15D; C_0201_0603Metric_L
C50: GRM21BR61A476ME15L; C_0805_2012Metric_L
D1: LXZ1-PR01; LED_LXZ1_PR01_L
J11, J12: DNL; Conn_1x1_250x750_Pad
R1: ERJ-1GNF1022C; R_0201_0603Metric_ERJ_L
R2, R3: ERJ-1GNF1002C; R_0201_0603Metric_ERJ_L
U2: LTC3218; SON_11_P50_300X200X80L40X25T239X64L
U3: TPL0102-100RUCR; QFN_14_P40_200X200X40L40X20L
U4: HV892; SON11P65_400X400X80L40X30T315X255L

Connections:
+3V3: C1.1, C4.1, C6.1, C50.1, R2.2, R3.2, U2.10, U3.1, U3.14, U4.2, U4.5
/EWL1: J11.1, U4.8
/EWL2: J12.1, U4.7
/I_SET: R1.2, U2.5, U2.6
/SCL_3V3: R3.1, U3.10, U4.3
/SDA_3V3: R2.1, U3.9, U4.4
GND: C1.2, C2.2, C4.2, C5.2, C6.2, C50.2, D1.C, U2.7, U2.8, U2.11, U3.2, U3.5, U3.7, U3.8, U3.11, U3.12, U3.13, U4.1, U4.6
unnamed: C2.1, U4.10
unnamed: C3.1, U2.9
unnamed: C3.2, U2.1
unnamed: C5.1, U2.2
unnamed: D1.A, U2.3
unnamed: R1.1, U3.6
unnamed: U3.3, U3.4

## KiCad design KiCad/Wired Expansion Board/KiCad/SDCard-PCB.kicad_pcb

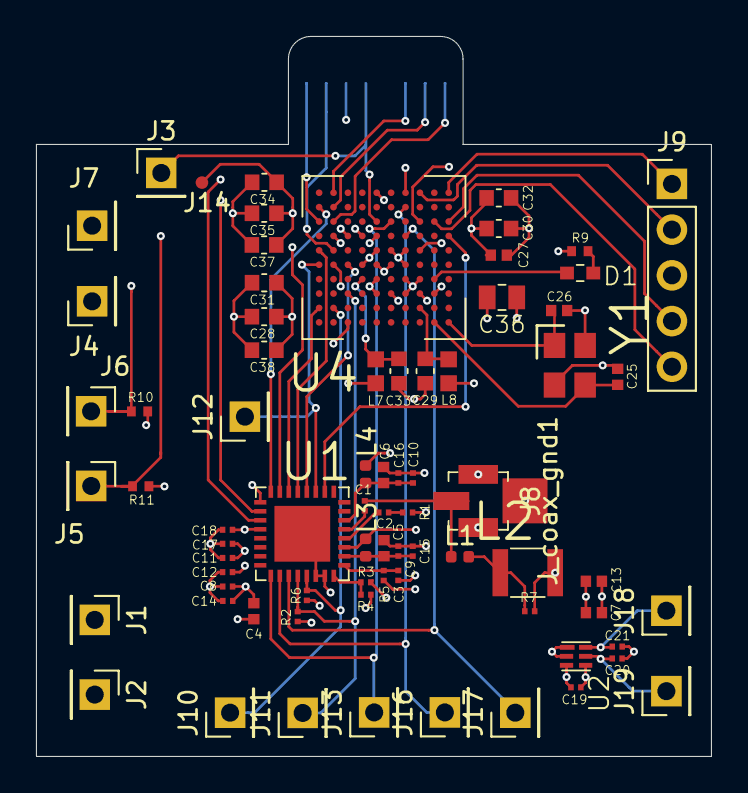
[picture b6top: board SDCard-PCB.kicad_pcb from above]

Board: 4 copper layers, 37.5 x 40.0 mm, 76 parts (1 on the bottom side), 47 nets.

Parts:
C1, C8, C9, C10, C11, C12: GRM033R61A104ME15D; C_0201_0603Metric_L
C2: GRM033R61C473KE84D; C_0201_0603Metric_L
C3, C19, C20, C21: GRM033R61A105ME15D; C_0201_0603Metric_L
C4, C5: GRM155R60J475ME47D; C_0402_1005Metric_L
C6: GRJ155R60J106ME11D; C_0402_1005Metric_L
C7, C13: GRM155R60J106ME15D; C_0402_1005Metric_L
C14, C15, C16, C17, C18: GRM033R71A103KA01D; C_0201_0603Metric_L
C25, C26: GRM1555C1H120JA01D; C_0402_1005Metric_L
C27: GRM155R60J475ME87D; C_0402_1005Metric_L
C28, C29, C30, C31, C32, C33, C34, C35, C37, C38: GCJ188R71E104KA12D; C_0603_1608Metric_L
C36: GCM21BR71E105KA56L; C_0805_2012Metric_L
D1: Vishay / Lite-On LTST-C191KRKT; LED_SC80X160X65L40L
J1, J2, J3, J4, J5, J6, J7, J10, J11, J12, J13, J16, J17, J18, J19: Conn_01x01; PinHeader_1x01_P2.54mm_Vertical
J8: Conn_Coaxial; U_FL-R-SMT_10_
J9: Conn_01x05; PinHeader_1x05_P2.54mm_Vertical
J14: Conn_01x01; Conn_1x1_700_Circular_Pad
J15: Conn_01x08; 1x8_microSD
J_coax_gnd1: Conn_01x01; Conn_1x1_1mmx1mm_Pad
L1, L3, L4: BLM15HD102SN1D; L_0402_1005Metric
L2: ADL3225V-470MT-TL000; L_1210_3225Metric_L
L7, L8: BLM18PG471SN1D; L_0603_1608Metric_L
R1: ERJ-1GEF49R9C; R_0201_0603Metric_ERJ_L
R2, R6: ERJ-1GEF3321C; R_0201_0603Metric_ERJ_L
R3, R5: ERJ-1GEF1002C; R_0201_0603Metric_ERJ_L
R4: ERJ-1GEF1003C; R_0201_0603Metric_ERJ_L
R7: MMBT3904LP-7B; R_0201_0603Metric_ERJ_L
R9: 499; R_0402_1005Metric_ERJ_L
R10, R11: 100k; R_0402_1005Metric_ERJ_L
U1: DS90UB933-Q1; QFN_33_P50_500X500X80L40X24T310L
U2: TLV7103318DSER; SON_6_P50_150X150X80L50X25L
U4: ATSAME70N21A-CN; BGA_100_CP80_10X10_900X900X110B40L
Y1: ABM8G-12.000MHZ-4Y-T3; OSCCC320X250X100L80X100

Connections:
+1V2: C34.1, C35.1, C36.1, C37.1, J14.1, L7.1, L8.2, U4.C3, U4.C6, U4.D6, U4.G6
+1V8: C4.1, C8.1, C12.1, C14.1, C18.1, C20.1, J2.1, J19.1, L3.2, L4.2, R3.1, U1.11, U1.28, U2.5
+3V3: C11.1, C17.1, C21.1, C27.1, C28.1, C30.1, C31.1, C32.1, C38.1, J1.1, J4.1, J18.1, R2.1, R5.1, R6.1, R10.1, R11.1, U1.25, U2.6, U4.C2, U4.C5, U4.E5, U4.E6, U4.F3, U4.G7
+5V: C7.1, C13.1, C19.1, L2.2, R7.1, U2.1, U2.2, U2.3
/Connectors/SWDCLK-Rec: J6.1, R10.2, U4.E9
/Connectors/SWDIO-Rec: J5.1, R11.2, U4.G8
/OnBoardMCU/FRAME_VALID: J16.1, U1.2, U4.J4
/OnBoardMCU/IMG_out0: J12.1, U1.19, U4.E10
/OnBoardMCU/IMG_out1: U1.20, U4.E8
/OnBoardMCU/IMG_out2: U1.21, U4.F10
/OnBoardMCU/IMG_out3: U1.22, U4.B10
/OnBoardMCU/IMG_out4: U1.23, U4.G9
/OnBoardMCU/IMG_out5: U1.24, U4.J10
/OnBoardMCU/IMG_out6: U1.26, U4.K6
/OnBoardMCU/IMG_out7: U1.27, U4.K4
/OnBoardMCU/LINE_VALID: J13.1, U1.1, U4.H5
/OnBoardMCU/PXL_CLK: J17.1, U1.3, U4.G4
/OnBoardMCU/RED_LED: D1.2, U4.D2
/OnBoardMCU/SCL: J11.1, R2.2, U1.4, U4.C8
/OnBoardMCU/SDA: J10.1, R6.2, U1.5, U4.B9
/OnBoardMCU/SER_CLK: U1.18, U4.G1
/OnBoardMCU/VDDPLL: C33.1, L7.2, U4.D7
/OnBoardMCU/VDDUTMIC: C29.1, L8.1, U4.B3
/OnBoardMCU/WXB_CLK: J3.1, J15.5, U4.H6
/OnBoardMCU/WXB_CMD: J15.3, U4.K9
/OnBoardMCU/WXB_in0: J15.7, U4.F9
/OnBoardMCU/WXB_in1: J15.8, U4.H10
/OnBoardMCU/WXB_in2: J15.1, U4.H9
/OnBoardMCU/WXB_in3: J15.2, U4.J9
/OnBoardMCU/XIN: C26.1, U4.A1, Y1.1
/OnBoardMCU/XOUT: C25.1, U4.A2, Y1.3
/OnBoardMCU/test1: J9.1, U4.K1
/OnBoardMCU/test2: J9.2, U4.K3
/OnBoardMCU/test3: J9.3, U4.H3
/OnBoardMCU/test4: J9.4, U4.H1
/OnBoardMCU/test5: J9.5, U4.H2
/Serializer/DOUT_P: C1.1, J8.2, L1.1
/Serializer/MODE: R3.2, R4.1, U1.8
/Serializer/PDB: C3.1, R5.2, U1.9
/Serializer/VDDCML: C6.1, C10.1, C16.1, L4.1, U1.14
/Serializer/VDDPLL: C5.1, C9.1, C15.1, L3.1, U1.10
Earth: C3.2, C4.2, C5.2, C6.2, C7.2, C8.2, C9.2, C10.2, C11.2, C12.2, C13.2, C14.2, C15.2, C16.2, C17.2, C18.2, C19.2, C20.2, C21.2, C25.2, C26.2, C27.2, C28.2, C29.2, C30.2, C31.2, C32.2, C33.2, C34.2, C35.2, C36.2, C37.2, C38.2, J7.1, J8.1, J15.6, J_coax_gnd1.1, R1.1, R4.2, R9.2, U1.6, U1.7, U1.33, U2.4, U4.A8, U4.C4, U4.D3, U4.D4, U4.E4, U4.E7, U4.F4, U4.F5, U4.F6, Y1.2, Y1.4
unnamed: C1.2, U1.13
unnamed: C2.1, R1.2
unnamed: C2.2, U1.12
unnamed: D1.1, R9.1
unnamed: L1.2, L2.1, R7.2

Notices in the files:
parts and their libraries:
Copyright 2016 Accelerated Designs. All rights reserved.
